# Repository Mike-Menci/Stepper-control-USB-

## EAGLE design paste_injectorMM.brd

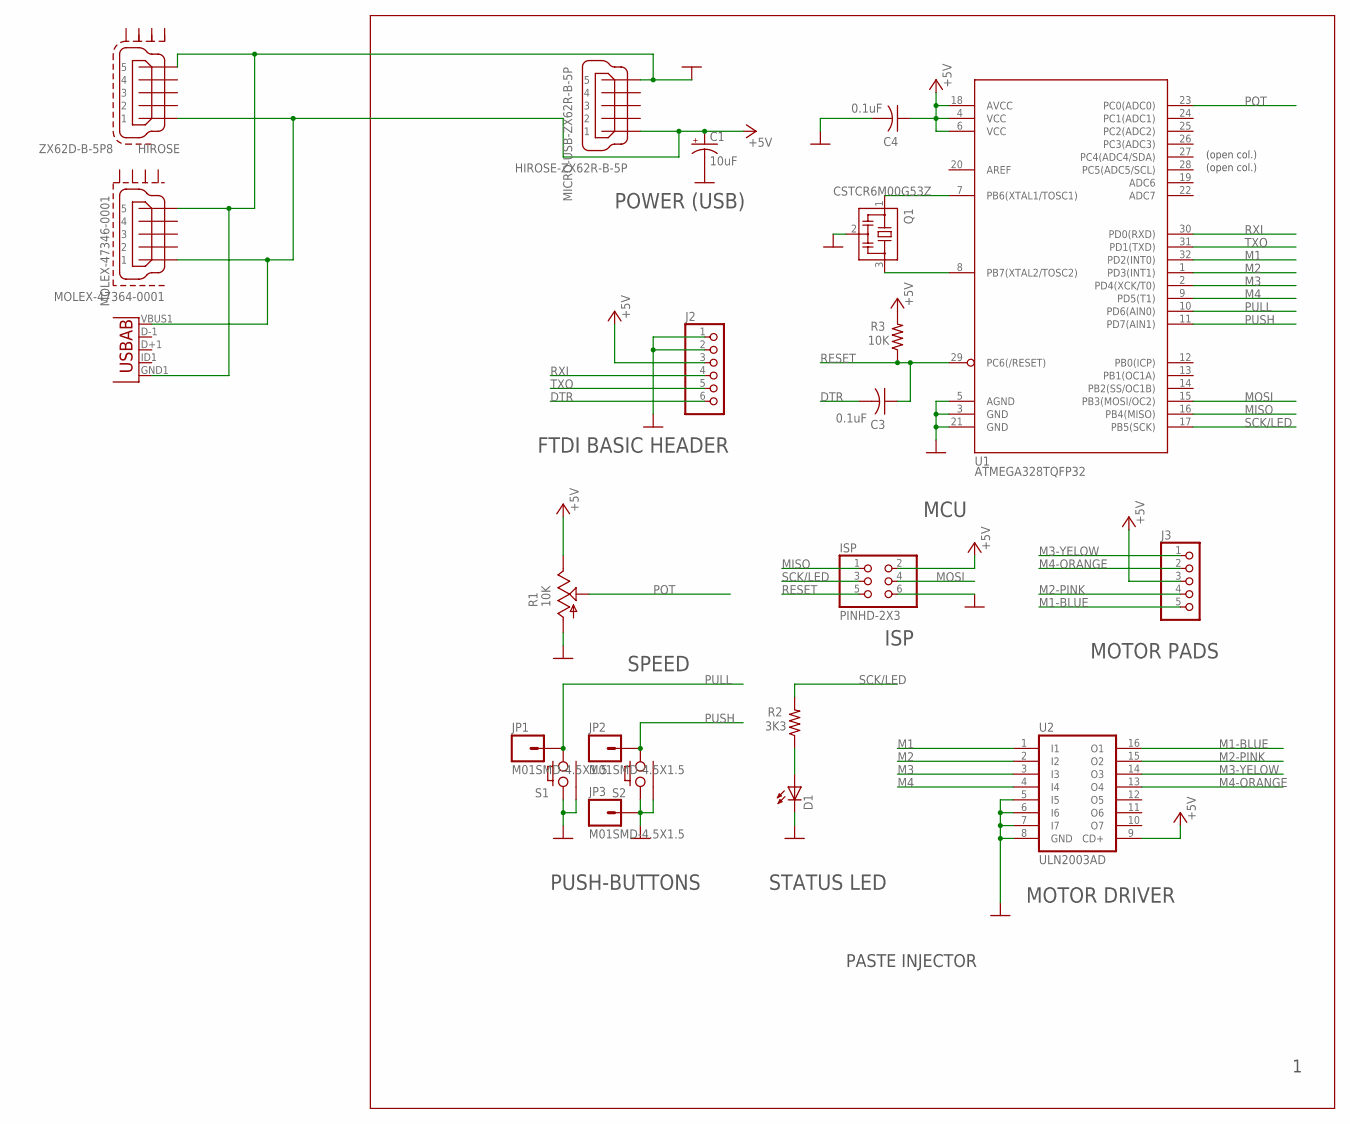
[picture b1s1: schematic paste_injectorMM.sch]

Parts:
C1: 10uF; A/3216-18R
C3, C4: 0.1uF; C0603
D1: LED; LED0603
HIROSE: ZX62D-B-5P8
HIROSE-ZX62R-B-5P: MICRO-USB-ZX62R-B-5P; ZX62R-B-5P
ISP: PINHD-2X3; 2X03
J2: PINHD-1X6; 1X06
J3: PINHD-1X5; 1X05
JP1, JP2, JP3: M01SMD-4.5X1.5; PAD-1.5X4.5
MOLEX-47364-0001: MOLEX-47346-0001; MOLEX-47364-0001
Q1: CSTCR6M00G53Z; CSTCR6M
R1: 10K; TRIMPOT
R2: 3K3; R0603
R3: 10K; R0603
S1, S2: PUSH_BUTTON
U1: ATMEGA328TQFP32; TQFP32-08
U2: ULN2003AD; SO16
U$7: USB-AB""; USB-AB-MICRO-SMD_V02_BOSS

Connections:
+5V: C1.+, C4.1, HIROSE.P$1 (1), HIROSE-ZX62R-B-5P.1, ISP.2, J2.3, J3.3, MOLEX-47364-0001.1, R1.CW, R3.2, U1.4 (VCC), U1.6 (VCC), U1.18 (AVCC), U2.9 (CD+), U$7.VBUS1 (VBUS)
DTR: C3.2, J2.6
GND: C1.-, C4.2, D1.C, HIROSE.P$5 (5), HIROSE-ZX62R-B-5P.5, ISP.6, J2.1, J2.2, JP3.P$1, MOLEX-47364-0001.5, Q1.2, R1.CCW, S1.A1 (1), S1.GND, S2.A1 (1), S2.GND, U1.3 (GND), U1.5 (AGND), U1.21 (GND), U2.5 (I5), U2.6 (I6), U2.7 (I7), U2.8 (GND), U$7.GND1 (GND)
M1: U1.32 (PD2(INT0)), U2.1 (I1)
M1-BLUE: J3.5, U2.16 (O1)
M2: U1.1 (PD3(INT1)), U2.2 (I2)
M2-PINK: J3.4, U2.15 (O2)
M3: U1.2 (PD4(XCK/T0)), U2.3 (I3)
M3-YELOW: J3.1, U2.14 (O3)
M4: U1.9 (PD5(T1)), U2.4 (I4)
M4-ORANGE: J3.2, U2.13 (O4)
MISO: ISP.1, U1.16 (PB4(MISO))
MOSI: ISP.4, U1.15 (PB3(MOSI/OC2))
unnamed: D1.A, R2.1
unnamed: Q1.1, U1.7 (PB6(XTAL1/TOSC1))
unnamed: Q1.3, U1.8 (PB7(XTAL2/TOSC2))
POT: R1.C, U1.23 (PC0(ADC0))
PULL: JP1.P$1, S1.B1 (2), U1.10 (PD6(AIN0))
PUSH: JP2.P$1, S2.B1 (2), U1.11 (PD7(AIN1))
RESET: C3.1, ISP.5, R3.1, U1.29 (PC6(/RESET))
RXI: J2.4, U1.30 (PD0(RXD))
SCK/LED: ISP.3, R2.2, U1.17 (PB5(SCK))
TXO: J2.5, U1.31 (PD1(TXD))

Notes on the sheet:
PASTE INJECTOR
ISP
POWER (USB)
SPEED
MOTOR DRIVER
MCU
MOTOR PADS
(open col.)
FTDI BASIC HEADER
STATUS LED
PUSH-BUTTONS

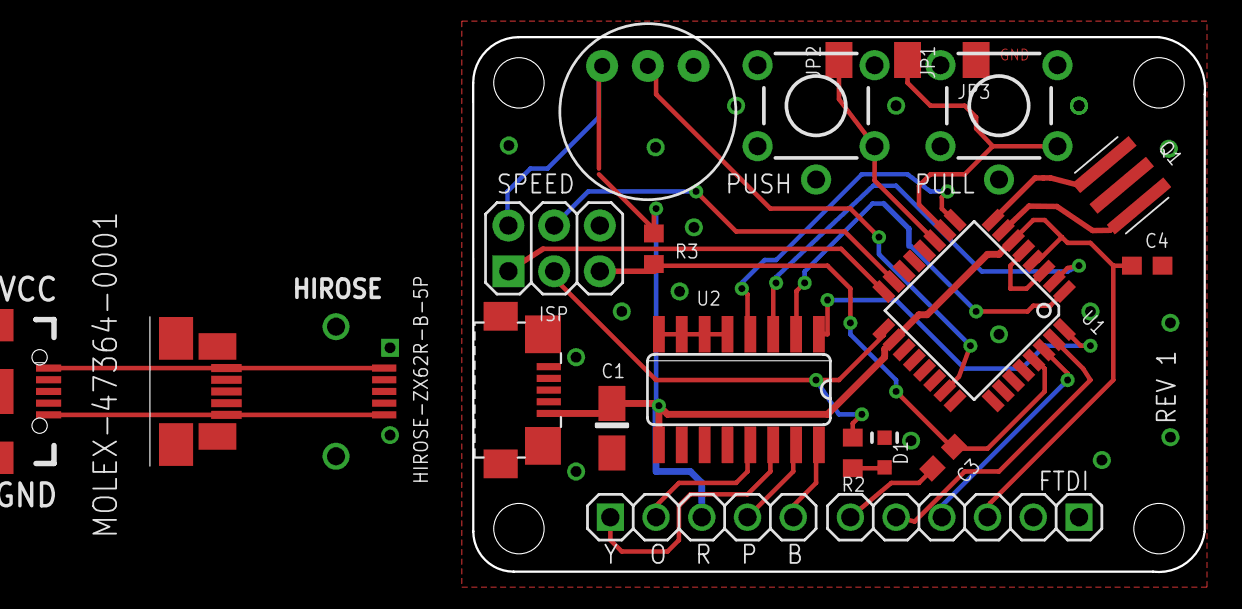
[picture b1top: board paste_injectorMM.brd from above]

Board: 2 copper layers, 40.7 x 29.7 mm, 26 parts (0 on the bottom side), 23 nets.

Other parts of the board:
U$2, U$3, U$4, U$5: 2,8

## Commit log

2015-10-24 EgleCad_USB
    Versions of USB, modified PCB, added GND, mount holes,...

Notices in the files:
parts and their libraries:
SparkFun-Connectors: Licensing: CC v3.0 Share-Alike You are welcome to use this library for commercial purposes.
